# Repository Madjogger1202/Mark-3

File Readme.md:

# Mark 3 — Robot Dog Control Board

> High-current RP2350B-based controller board for quadruped robots.  
> Integrated **battery protection**, **PD charging**, **per-leg power domains**, and **radio/IMU** subsystem.  
> Designed for compact 4-legged robots with modular legs and high servo load.

---

## What’s on the board
- **Main MCU:** RP2350B (USB-programmable)
- **Power system:**
  - **6 × 18650** cells in **parallel** (on-board holders)
  - **Protection IC:** DW01 for undervoltage / overcurrent safety  
  - **USB Type-C PD** charging via **HUSB237-AA001-DN06R** (default 15 V profile, configurable)
  - **Battery charger:** BQ24610, up to **10 A charge current**
  - **Four TPS61088** boost converters — each provides **6 V / 10 A** per leg
  - Individual **enable lines** for each leg’s converter
  - **Current-sense** circuit per leg power rail
- **IMU:** LSM6DS3 (SPI interface)
- **Radio:** nRF24L01P (integrated 2.4 GHz transceiver)
- **LED indication:**
  - 8 × battery-level LEDs
  - 2 × status LEDs (power / charging / fault)
- **Two separate USB-C ports:**
  - **Programming** (direct to RP2350B)
  - **Charging** (PD trigger + BQ24610)
- **BOOT** button for UF2 flashing  
- All power and signal routing optimized for servo current spikes

---

## Power System Overview
| Function | Component | Voltage | Current | Notes |
|:--|:--|:--|:--|:--|
| PD Trigger | HUSB237-AA001-DN06R | 15 V (default) | up to 3 A | Configurable by resistors |
| Charger | BQ24610 | 15 V → Battery | up to 10 A | 1S6P Li-ion |
| Protection | DW01 | 1S | — | Undervoltage / overcurrent cutoff |
| Boost × 4 | TPS61088 | 6 V | 10 A each | One per leg |
| MCU & Logic | RP2350B + LDO | 3.3 V | — | Isolated domain |

> ⚠️ **Do not** connect external 5 V to the MCU port while PD charging.  
> Power and data paths are separate to prevent back-feed.

---

## Sensors & Interfaces
- **LSM6DS3 (SPI)** — motion sensing (accelerometer + gyroscope)  
- **nRF24L01P (SPI)** — wireless communication  
- Expansion headers for extra sensors (I²C / SPI / UART)  
- Servo outputs grouped per leg (3 per leg × 4 legs)

---

## Battery Section
- 6 × **18650 cells in parallel**
- **DW01** provides basic protection (no balancing)
- On-board holders for easy replacement
- **LED bar (8 segments)** for charge level indication

---

## Quick Use
1. Insert 6× 18650 cells into holders.  
2. Connect USB-C **charging** port (PD trigger negotiates 15 V).  
3. Wait for charge LEDs to show full battery.  
4. Connect USB-C **programming** port to PC.  
5. Hold **BOOT** and power the board to enter UF2 mode.  
6. Flash firmware to RP2350B.  
7. Control each leg’s power domain and read current measurements as needed.

---

## Typical Applications
- Quadruped robots (up to 4 legs, 3 servos per leg)
- High-current servo testing rigs
- Portable motion control platforms
- Development base for RP2350 motion control firmware

---

## Notes
- Each leg’s 6 V converter (TPS61088) can be disabled via GPIO.  
- Charging and MCU USB ports are independent.  
- PD trigger default = 15 V (can be changed by resistor network).  
- Full pinout and schematics in `/docs/Mark3_schematic.pdf`.

---

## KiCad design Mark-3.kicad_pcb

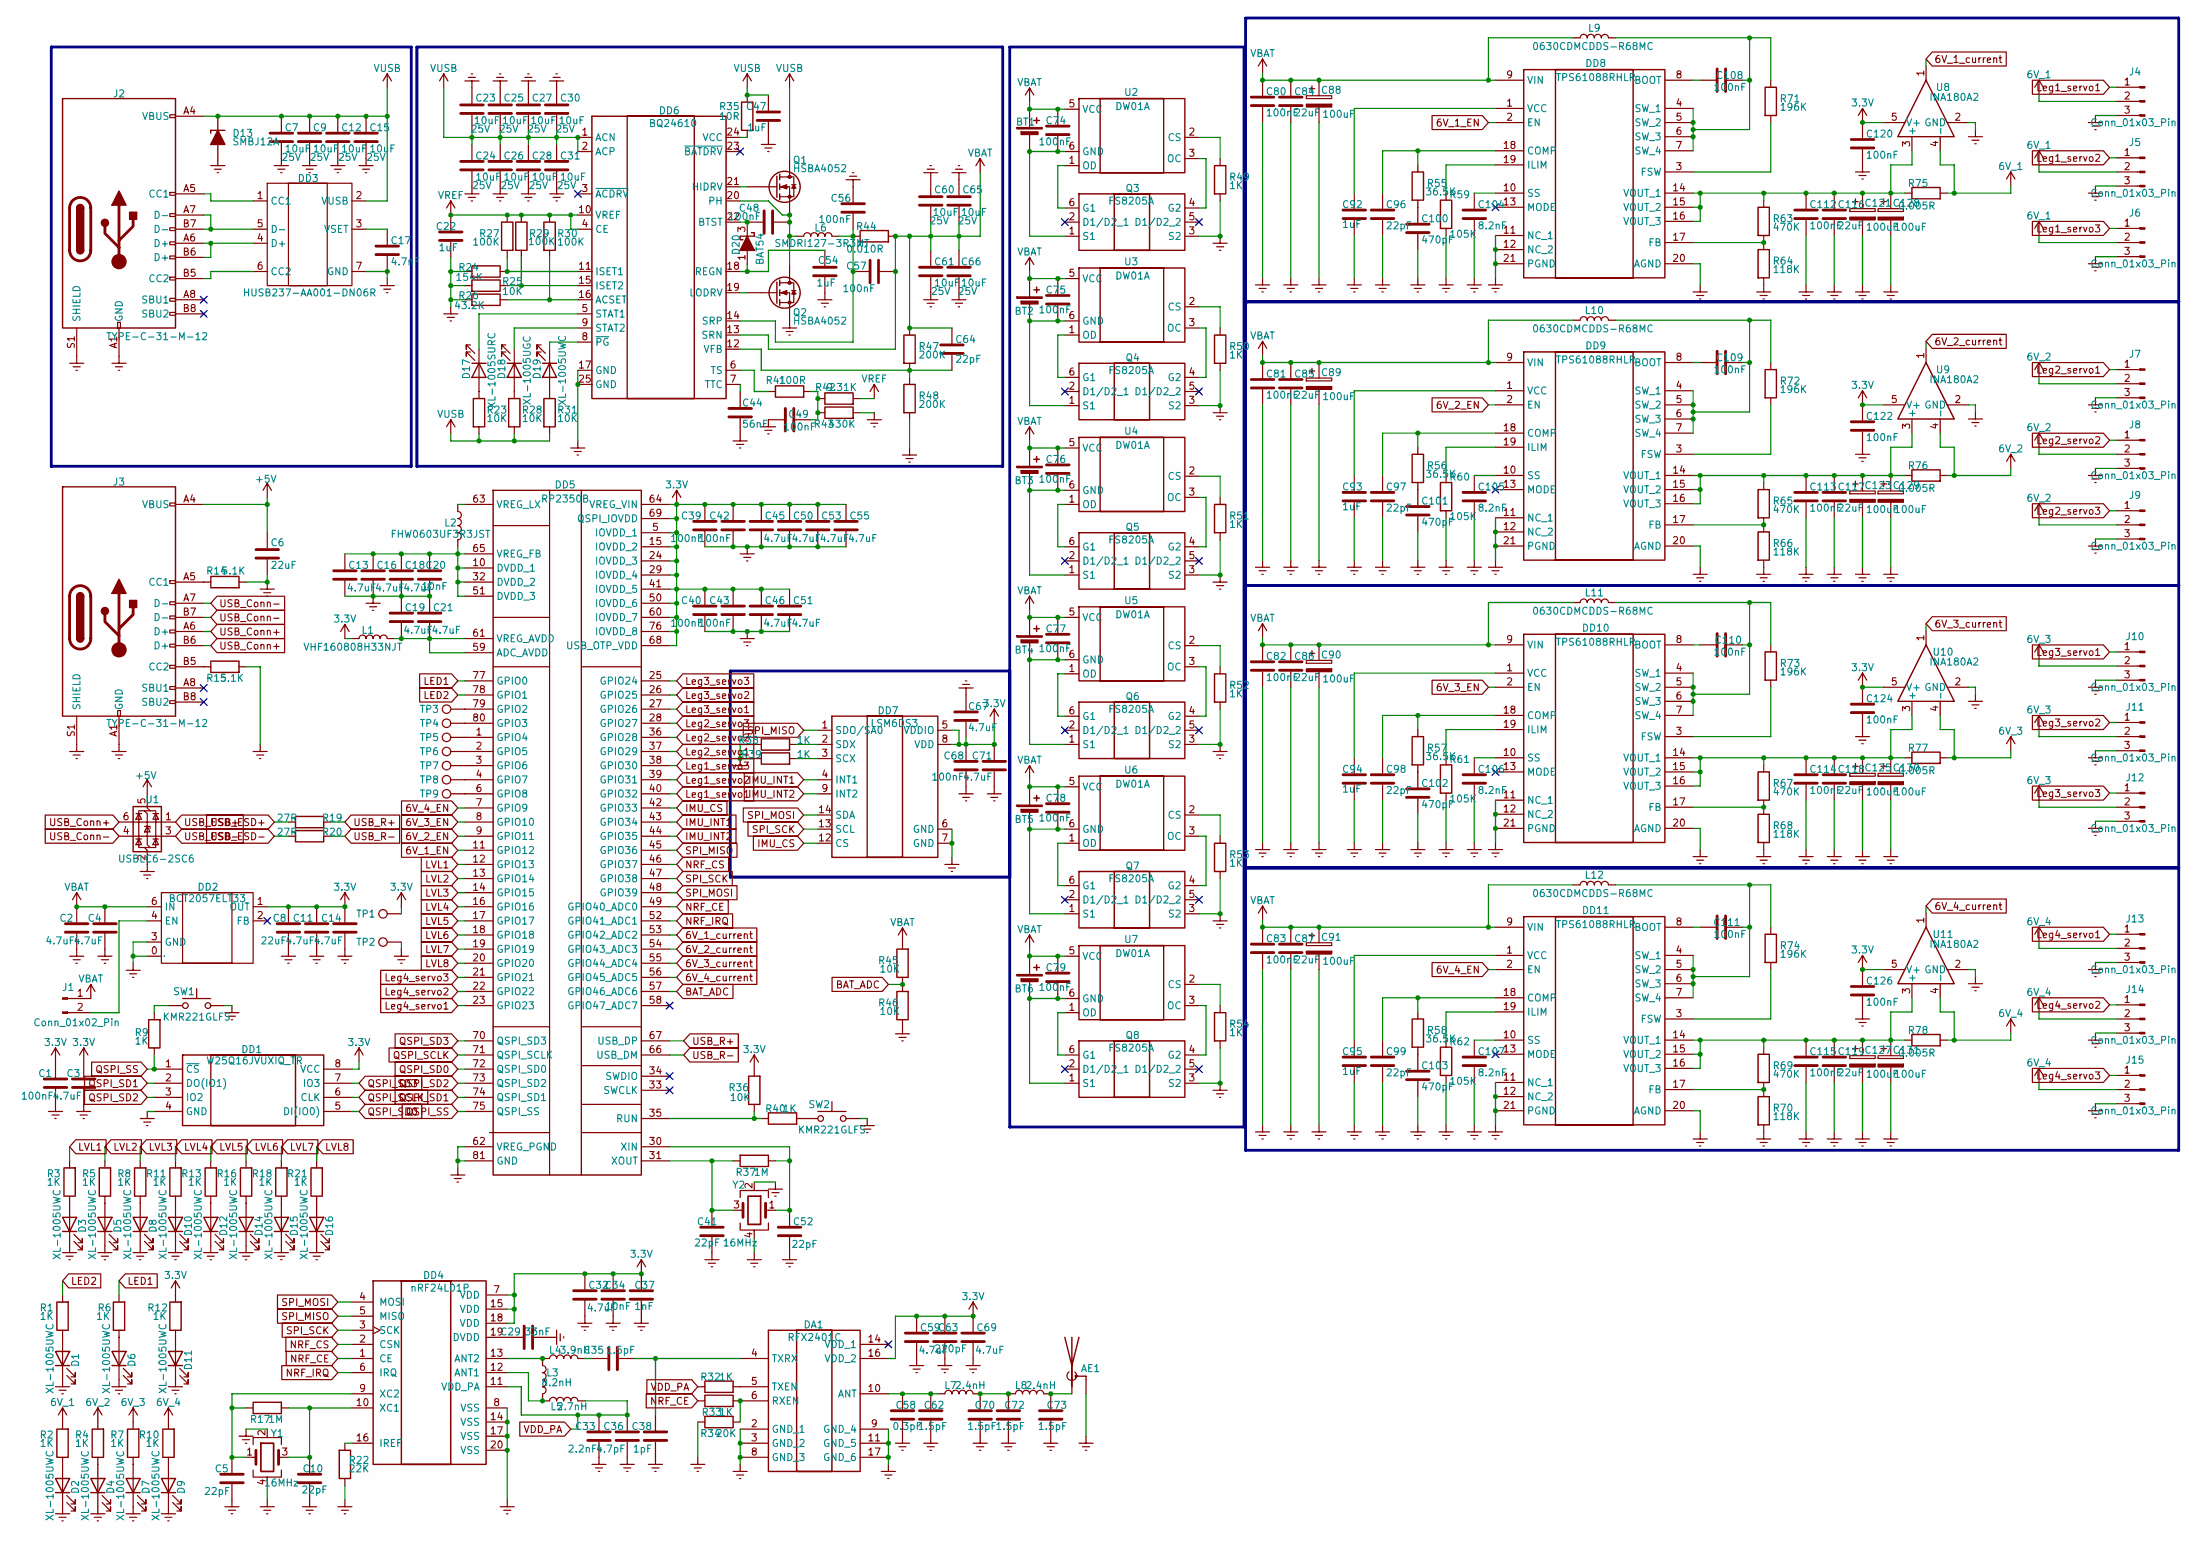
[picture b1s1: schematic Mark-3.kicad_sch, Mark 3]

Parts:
AE1: Antenna_Shield; Texas_SWRA117D_2.4GHz_Right
BT1, BT2, BT3, BT4, BT5, BT6: Battery_Cell; BatteryHolder_Keystone_1042_1x18650
C1, C39, C40, C42, C43, C68: 100nF; C_0201_0603Metric
C2, C3, C4, C11, C13, C14, C16, C18, C19, C21, C32, C45, C46, C50, C51, C53, C55, C59, C67, C69, C71: 4.7uF; C_0201_0603Metric
C5, C10, C41, C52: 22pF; C_0201_0603Metric
C6, C8: 22uF; C_0402_1005Metric
C7, C9, C12, C15, C23, C24, C25, C26, C27, C28, C30, C31, C60, C61, C65, C66: 10uF; C_0805_2012Metric; Voltage 25V; JLCPCB part C5674
C17: 4.7nF; C_0402_1005Metric; JLCPCB part C5674
C20, C34: 10nF; C_0201_0603Metric
C22, C47, C54, C92, C93, C94, C95: 1uF; C_0402_1005Metric; JLCPCB part C5674
C29: 33nF; C_0201_0603Metric
C33: 2.2nF; C_0201_0603Metric
C35, C62, C70, C72, C73: 1.5pF; C_0201_0603Metric
C36: 4.7pF; C_0201_0603Metric
C37: 1nF; C_0201_0603Metric
C38: 1pF; C_0201_0603Metric
C44: 56nF; C_0402_1005Metric; JLCPCB part C5674
C48, C49, C56, C57, C74, C75, C76, C77, C78, C79, C80, C81, C82, C83, C108, C109, C110, C111, C112, C113, C114, C115, C120, C122, C124, C126: 100nF; C_0402_1005Metric; JLCPCB part C5674
C58: 0.3pF; C_0201_0603Metric
C63: 220pF; C_0201_0603Metric
C64, C96, C97, C98, C99: 22pF; C_0402_1005Metric; JLCPCB part C5674
C84, C85, C86, C87, C116, C117, C118, C119: 22uF; C_0805_2012Metric; JLCPCB part C5674
C88, C89, C90, C91, C121, C123, C125, C127, C128, C129, C130, C131: 100uF; CP_EIA-3528-21_Kemet-B; JLCPCB part C140381
C100, C101, C102, C103: 470pF; C_0402_1005Metric; JLCPCB part C5674
C104, C105, C106, C107: 8.2nF; C_0402_1005Metric; JLCPCB part C5674
D1, D2, D3, D4, D5, D6, D7, D8, D9, D10, D11, D12, D14, D15, D16, D19: XL-1005UWC; LED_0402_1005Metric
D13: SMBJ12A; D_SMB
D17: XL-1005SURC; LED_0402_1005Metric
D18: XL-1005UGC; LED_0402_1005Metric
D20: BAT54; SOT-23
DA1: RFX2401C; Manufacturer_Part_Number RFX2401C; Mouser Part Number 477-RFX2401C
DD1: W25Q16JVUXIQ_TR; W25Q16JVUXIQ; Manufacturer_Part_Number W25Q16JVUXIQ TR; Mouser Part Number 454-W25Q16JVUXIQTR
DD2: BCT2057ELT33; BCT2057ELTAJ; Manufacturer Part BCT2057ELTAJ-TR; LCSC Part Name 1A, 低 dropout 线性稳压器
DD3: HUSB237-AA001-DN06R; Manufacturer Part HUSB237-AA001-DN06R; LCSC Part Name HUSB237-AA001-DN06R
DD4: nRF24L01P; QFN-20-1EP_4x4mm_P0.5mm_EP2.5x2.5mm
DD5: RP2350B; QFN40P1000X1000X90-81N-D; Manufacturer_Part_Number RP2350B
DD6: BQ24610; VQFN-24-1EP_4x4mm_P0.5mm_EP2.45x2.45mm
DD7: LSM6DS3; LGA-14_3x2.5mm_P0.5mm_LayoutBorder3x4y
DD8, DD9, DD10, DD11: TPS61088RHLR; Manufacturer_Part_Number TPS61088RHLR; Mouser Part Number 595-TPS61088RHLR
J1: Conn_01x02_Pin; PinHeader_1x02_P2.54mm_Vertical
J2: TYPE-C-31-M-12; USB_C_Receptacle_G-Switch_GT-USB-7010ASV
J3: TYPE-C-31-M-12; USB_C_Receptacle_GCT_USB4105-xx-A_16P_TopMnt_Horizontal
J4, J5, J6, J7, J8, J9, J10, J11, J12, J13, J14, J15: Conn_01x03_Pin; PinHeader_1x03_P2.54mm_Vertical
L1: VHF160808H33NJT; L_0603_1608Metric
L2: FHW0603UF3R3JST; L_0603_1608Metric
L3: 8.2nH; L_0201_0603Metric
L4: 3.9nH; L_0201_0603Metric
L5: 2.7nH; L_0201_0603Metric
L6: SMDRI127-3R3MT; L_SXN_SMDRI127
L7, L8: 2.4nH; L_0201_0603Metric
L9, L10, L11, L12: 0630CDMCDDS-R68MC; L_Sunlord_MWSA0603S
Q1, Q2: HSBA4052; PQFN-8-EP_6x5mm_P1.27mm_Generic
Q3, Q4, Q5, Q6, Q7, Q8: FS8205A; Manufacturer_Part_Number FS8205A
R1, R2, R3, R4, R5, R6, R7, R8, R10, R11, R12, R13, R16, R18, R21, R49, R50, R51, R52, R53, R54: 1K; R_0402_1005Metric
R9, R32, R33, R38, R39, R40: 1K; R_0201_0603Metric
R14, R15: 5.1K; R_0402_1005Metric
R17, R37: 1M; R_0201_0603Metric
R19, R20: 27R; R_0201_0603Metric
R22: 22K; R_0201_0603Metric
R23, R25, R28, R31: 10K; R_0402_1005Metric
R24: 154K; R_0402_1005Metric
R26: 43.2K; R_0402_1005Metric
R27, R29, R30: 100K; R_0402_1005Metric
R34: 20K; R_0201_0603Metric
R35: 10R; R_0402_1005Metric
R36, R45, R46: 10K; R_0201_0603Metric
R41: 100R; R_0402_1005Metric
R42: 9.31K; R_0402_1005Metric
R43: 430K; R_0402_1005Metric
R44: 0.010R; R_2512_6332Metric_Pad1.40x3.35mm
R47, R48: 200K; R_0402_1005Metric
R55, R56, R57, R58: 36.5K; R_0402_1005Metric
R59, R60, R61, R62: 105K; R_0402_1005Metric
R63, R65, R67, R69: 470K; R_0402_1005Metric
R64, R66, R68, R70: 118K; R_0402_1005Metric
R71, R72, R73, R74: 196K; R_0402_1005Metric
R75, R76, R77, R78: 0.005R; R_1206_3216Metric
SW1, SW2: KMR221GLFS; SW_SPST_PTS810
TP1, TP2, TP3, TP4, TP5, TP6, TP7, TP8, TP9: TestPoint; TestPoint_Pad_D1.0mm
U1: USBLC6-2SC6; SOT-23-6
U2, U3, U4, U5, U6, U7: DW01A; SOT-23-6
U8, U9, U10, U11: INA180A2; SOT-23-5
Y1, Y2: 16MHz; Crystal_SMD_3225-4Pin_3.2x2.5mm

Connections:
3.3V: C1.1, C3.1, C8.1, C11.1, C14.1, C32.1, C34.1, C37.1, C39.1, C40.1, C42.1, C43.1, C45.1, C46.1, C50.1, C51.1, C53.1, C55.1, C59.1, C63.1, C67.1, C68.1, C69.1, C71.1, C120.1, C122.1, C124.1, C126.1, DA1.16 (VDD_2), DD1.8 (VCC), DD2.1 (OUT), DD4.7 (VDD), DD4.15 (VDD), DD4.18 (VDD), DD5.5 (IOVDD_1), DD5.15 (IOVDD_2), DD5.24 (IOVDD_3), DD5.29 (IOVDD_4), DD5.41 (IOVDD_5), DD5.50 (IOVDD_6), DD5.60 (IOVDD_7), DD5.64 (VREG_VIN), DD5.68 (USB_OTP_VDD), DD5.69 (QSPI_IOVDD), DD5.76 (IOVDD_8), DD7.5 (VDDIO), DD7.8 (VDD), L1.1, R12.2, R36.2, TP1.1, U8.5 (V+), U9.5 (V+), U10.5 (V+), U11.5 (V+)
6V_1: J4.2, J5.2, J6.2, R2.2, R75.2, U8.4 (-)
6V_1_EN: DD5.11 (GPIO12), DD8.2 (EN)
6V_1_current: DD5.53 (GPIO42_ADC2), U8.1
6V_2: J7.2, J8.2, J9.2, R4.2, R76.2, U9.4 (-)
6V_2_EN: DD5.9 (GPIO11), DD9.2 (EN)
6V_2_current: DD5.54 (GPIO43_ADC3), U9.1
6V_3: J10.2, J11.2, J12.2, R7.2, R77.2, U10.4 (-)
6V_3_EN: DD5.8 (GPIO10), DD10.2 (EN)
6V_3_current: DD5.55 (GPIO44_ADC4), U10.1
6V_4: J13.2, J14.2, J15.2, R10.2, R78.2, U11.4 (-)
6V_4_EN: DD5.7 (GPIO9), DD11.2 (EN)
6V_4_current: DD5.56 (GPIO45_ADC5), U11.1
+5V: C6.1, J3.A4 (VBUS), J3.A9 (VBUS), J3.B4 (VBUS), J3.B9 (VBUS), U1.5 (VBUS)
BAT_ADC: DD5.57 (GPIO46_ADC6), R45.1, R46.2
Earth: AE1.2 (Shield), C1.2, C2.2, C3.2, C4.2, C5.2, C6.2, C7.2, C8.2, C9.2, C10.2, C11.2, C12.2, C13.2, C14.2, C15.2, C16.2, C17.2, C18.2, C19.1, C20.2, C21.1, C22.2, C23.2, C24.2, C25.2, C26.2, C27.2, C28.2, C29.2, C30.2, C31.2, C32.2, C33.2, C34.2, C36.2, C37.2, C38.2, C39.2, C40.2, C41.2, C42.2, C43.2, C44.2, C45.2, C46.2, C47.1, C49.1, C50.2, C51.2, C52.2, C53.2, C54.1, C55.2, C56.2, C58.2, C59.2, C60.2, C61.2, C62.2, C63.2, C65.2, C66.2, C67.2, C68.2, C69.2, C70.2, C71.2, C72.2, C73.2, C80.2, C81.2, C82.2, C83.2, C84.2, C85.2, C86.2, C87.2, C88.2, C89.2, C90.2, C91.2, C92.2, C93.2, C94.2, C95.2, C96.2, C97.2, C98.2, C99.2, C100.2, C101.2, C102.2, C103.2, C104.2, C105.2, C106.2, C107.2, C112.2, C113.2, C114.2, C115.2, C116.2, C117.2, C118.2, C119.2, C120.2, C121.2, C122.2, C123.2, C124.2, C125.2, C126.2, C127.2, C128.2, C129.2, C130.2, C131.2, D1.1 (K), D2.1 (K), D3.1 (K), D4.1 (K), D5.1 (K), D6.1 (K), D7.1 (K), D8.1 (K), D9.1 (K), D10.1 (K), D11.1 (K), D12.1 (K), D13.2 (A), D14.1 (K), D15.1 (K), D16.1 (K), DA1.2 (GND_1), DA1.3 (GND_2), DA1.8 (GND_3), DA1.9 (GND_4), DA1.11 (GND_5), DA1.17 (GND_6), DD1.4 (GND), DD2.0 (EP), DD2.3 (GND), DD3.7 (GND), DD4.8 (VSS), DD4.14 (VSS), DD4.17 (VSS), DD4.20 (VSS), DD4.21 (PAD), DD5.62 (VREG_PGND), DD5.81 (GND), DD6.17 (GND), DD6.25 (GND), DD7.6 (GND), DD7.7 (GND), DD8.11 (NC_1), DD8.12 (NC_2), DD8.20 (AGND), DD8.21 (PGND), DD9.11 (NC_1), DD9.12 (NC_2), DD9.20 (AGND), DD9.21 (PGND), DD10.11 (NC_1), DD10.12 (NC_2), DD10.20 (AGND), DD10.21 (PGND), DD11.11 (NC_1), DD11.12 (NC_2), DD11.20 (AGND), DD11.21 (PGND), J2.A1 (GND), J2.A12 (GND), J2.B1 (GND), J2.B12 (GND), J2.S1 (SHIELD), J3.A1 (GND), J3.A12 (GND), J3.B1 (GND), J3.B12 (GND), J3.S1 (SHIELD), J4.3, J5.3, J6.3, J7.3, J8.3, J9.3, J10.3, J11.3, J12.3, J13.3, J14.3, J15.3, Q2.1 (S), Q2.2 (S), Q2.3 (S), Q3.3 (S2), Q4.3 (S2), Q5.3 (S2), Q6.3 (S2), Q7.3 (S2), Q8.3 (S2), R14.2, R15.2, R22.1, R24.2, R25.2, R26.2, R34.2, R38.1, R39.1, R43.2, R46.1, R48.2, R49.2, R50.2, R51.2, R52.2, R53.2, R54.2, R59.2, R60.2, R61.2, R62.2, R64.2, R66.2, R68.2, R70.2, SW1.1, SW2.1, TP2.1, U1.2 (GND), U8.2 (GND), U9.2 (GND), U10.2 (GND), U11.2 (GND), Y1.2, Y1.4, Y2.2, Y2.4
IMU_CS: DD5.42 (GPIO33), DD7.12 (CS)
IMU_INT1: DD5.43 (GPIO34), DD7.4 (INT1)
IMU_INT2: DD5.44 (GPIO35), DD7.9 (INT2)
LED1: DD5.77 (GPIO0), R6.2
LED2: DD5.78 (GPIO1), R1.2
LVL1: DD5.12 (GPIO13), R3.2
LVL2: DD5.13 (GPIO14), R5.2
LVL3: DD5.14 (GPIO15), R8.2
LVL4: DD5.16 (GPIO16), R11.2
LVL5: DD5.17 (GPIO17), R13.2
LVL6: DD5.18 (GPIO18), R16.2
LVL7: DD5.19 (GPIO19), R18.2
LVL8: DD5.20 (GPIO20), R21.2
Leg1_servo1: DD5.40 (GPIO32), J4.1
Leg1_servo2: DD5.39 (GPIO31), J5.1
Leg1_servo3: DD5.38 (GPIO30), J6.1
Leg2_servo1: DD5.37 (GPIO29), J7.1
Leg2_servo2: DD5.36 (GPIO28), J8.1
Leg2_servo3: DD5.28 (GPIO27), J9.1
Leg3_servo1: DD5.27 (GPIO26), J10.1
Leg3_servo2: DD5.26 (GPIO25), J11.1
Leg3_servo3: DD5.25 (GPIO24), J12.1
Leg4_servo1: DD5.23 (GPIO23), J13.1
Leg4_servo2: DD5.22 (GPIO22), J14.1
Leg4_servo3: DD5.21 (GPIO21), J15.1
NRF_CE: DD4.1 (CE), DD5.49 (GPIO40_ADC0), R33.1
NRF_CS: DD4.2 (CSN), DD5.46 (GPIO37)
NRF_IRQ: DD4.6 (IRQ), DD5.52 (GPIO41_ADC1)
unnamed: AE1.1 (A), C73.1, L8.2
unnamed: BT1.2 (-), C74.2, Q3.1 (S1), U2.6 (GND)
unnamed: BT2.2 (-), C75.2, Q4.1 (S1), U3.6 (GND)
unnamed: BT3.2 (-), C76.2, Q5.1 (S1), U4.6 (GND)
unnamed: BT4.2 (-), C77.2, Q6.1 (S1), U5.6 (GND)
unnamed: BT5.2 (-), C78.2, Q7.1 (S1), U6.6 (GND)
unnamed: BT6.2 (-), C79.2, Q8.1 (S1), U7.6 (GND)
unnamed: C35.1, L4.2
unnamed: C49.2, R41.2, R42.1, R43.1
unnamed: C70.1, C72.1, L7.2, L8.1
unnamed: C100.1, R55.2
unnamed: C101.1, R56.2
unnamed: C102.1, R57.2
unnamed: C103.1, R58.2
unnamed: D1.2 (A), R1.1
unnamed: D2.2 (A), R2.1
unnamed: D3.2 (A), R3.1
unnamed: D4.2 (A), R4.1
unnamed: D5.2 (A), R5.1
unnamed: D6.2 (A), R6.1
unnamed: D7.2 (A), R7.1
unnamed: D8.2 (A), R8.1
unnamed: D9.2 (A), R10.1
unnamed: D10.2 (A), R11.1
unnamed: D11.2 (A), R12.1
unnamed: D12.2 (A), R13.1
unnamed: D14.2 (A), R16.1
unnamed: D15.2 (A), R18.1
unnamed: D16.2 (A), R21.1
unnamed: D17.2 (A), R23.1
unnamed: D17.1 (K), DD6.5 (STAT1)
unnamed: D18.2 (A), R28.1
unnamed: D18.1 (K), DD6.9 (STAT2)
unnamed: D19.2 (A), R31.1
unnamed: D19.1 (K), DD6.8 (~PG)
unnamed: C54.2, D20.1 (A), DD6.18 (REGN)
unnamed: C48.1, D20.3 (K), DD6.22 (BTST)
unnamed: C58.1, C62.1, DA1.10 (ANT), L7.1
unnamed: DA1.6 (RXEN), R33.2, R34.1
unnamed: DA1.5 (TXEN), R32.2
unnamed: C35.2, C38.1, DA1.4 (TXRX)
unnamed: DD2.4 (EN), J1.2
unnamed: DD3.1 (CC1), J2.A5 (CC1)
unnamed: DD3.6 (CC2), J2.B5 (CC2)
unnamed: DD3.4 (D+), J2.A6 (D+), J2.B6 (D+)
unnamed: DD3.5 (D-), J2.A7 (D-), J2.B7 (D-)
unnamed: C17.1, DD3.3 (VSET)
unnamed: DD4.12 (ANT1), L3.2, L5.1
unnamed: DD4.13 (ANT2), L3.1, L4.1
unnamed: C29.1, DD4.19 (DVDD)
unnamed: DD4.16 (IREF), R22.2
unnamed: C10.1, DD4.10 (XC1), R17.2, Y1.3
unnamed: C5.1, DD4.9 (XC2), R17.1, Y1.1
unnamed: C19.2, C21.2, DD5.59 (ADC_AVDD), DD5.61 (VREG_AVDD), L1.2
unnamed: C13.1, C16.1, C18.1, C20.1, DD5.10 (DVDD_1), DD5.32 (DVDD_2), DD5.51 (DVDD_3), DD5.65 (VREG_FB), L2.2
unnamed: DD5.79 (GPIO2), TP3.1
unnamed: DD5.80 (GPIO3), TP4.1
unnamed: DD5.1 (GPIO4), TP5.1
unnamed: DD5.2 (GPIO5), TP6.1
unnamed: DD5.3 (GPIO6), TP7.1
unnamed: DD5.4 (GPIO7), TP8.1
unnamed: DD5.6 (GPIO8), TP9.1
unnamed: DD5.35 (RUN), R36.1, R40.1
unnamed: DD5.63 (VREG_LX), L2.1
unnamed: C52.1, DD5.30 (XIN), R37.1, Y2.1
unnamed: C41.1, DD5.31 (XOUT), R37.2, Y2.3
unnamed: DD6.16 (ACSET), R26.1, R30.2
unnamed: DD6.21 (HIDRV), Q1.4 (G)
unnamed: DD6.11 (ISET1), R24.1, R27.2
unnamed: DD6.15 (ISET2), R25.1, R29.2
unnamed: DD6.19 (LODRV), Q2.4 (G)
unnamed: C56.1, C57.1, DD6.14 (SRP), L6.2, R44.1
unnamed: DD6.6 (TS), R41.1
unnamed: C44.1, DD6.7 (TTC)
unnamed: DD6.24 (VCC), R35.2
unnamed: C64.2, DD6.12 (VFB), R47.2, R48.1
unnamed: DD7.3 (SCX), R39.2
unnamed: DD7.2 (SDX), R38.2
unnamed: C108.1, DD8.8 (BOOT)
unnamed: C96.1, DD8.18 (COMP), R55.1
unnamed: DD8.17 (FB), R63.2, R64.1
unnamed: DD8.3 (FSW), R71.2
unnamed: DD8.19 (ILIM), R59.1
unnamed: C104.1, DD8.10 (SS)
unnamed: C108.2, DD8.4 (SW_1), DD8.5 (SW_2), DD8.6 (SW_3), DD8.7 (SW_4), L9.2, R71.1
unnamed: C92.1, DD8.1 (VCC)
unnamed: C112.1, C116.1, C121.1, C128.1, DD8.14 (VOUT_1), DD8.15 (VOUT_2), DD8.16 (VOUT_3), R63.1, R75.1, U8.3 (+)
unnamed: C109.1, DD9.8 (BOOT)
unnamed: C97.1, DD9.18 (COMP), R56.1
unnamed: DD9.17 (FB), R65.2, R66.1
unnamed: DD9.3 (FSW), R72.2
unnamed: DD9.19 (ILIM), R60.1
unnamed: C105.1, DD9.10 (SS)
unnamed: C109.2, DD9.4 (SW_1), DD9.5 (SW_2), DD9.6 (SW_3), DD9.7 (SW_4), L10.2, R72.1
unnamed: C93.1, DD9.1 (VCC)
unnamed: C113.1, C117.1, C123.1, C129.1, DD9.14 (VOUT_1), DD9.15 (VOUT_2), DD9.16 (VOUT_3), R65.1, R76.1, U9.3 (+)
unnamed: C110.1, DD10.8 (BOOT)
unnamed: C98.1, DD10.18 (COMP), R57.1
unnamed: DD10.17 (FB), R67.2, R68.1
unnamed: DD10.3 (FSW), R73.2
unnamed: DD10.19 (ILIM), R61.1
unnamed: C106.1, DD10.10 (SS)
unnamed: C110.2, DD10.4 (SW_1), DD10.5 (SW_2), DD10.6 (SW_3), DD10.7 (SW_4), L11.2, R73.1
unnamed: C94.1, DD10.1 (VCC)
unnamed: C114.1, C118.1, C125.1, C130.1, DD10.14 (VOUT_1), DD10.15 (VOUT_2), DD10.16 (VOUT_3), R67.1, R77.1, U10.3 (+)
unnamed: C111.1, DD11.8 (BOOT)
unnamed: C99.1, DD11.18 (COMP), R58.1
unnamed: DD11.17 (FB), R69.2, R70.1
unnamed: DD11.3 (FSW), R74.2
unnamed: DD11.19 (ILIM), R62.1
unnamed: C107.1, DD11.10 (SS)
unnamed: C111.2, DD11.4 (SW_1), DD11.5 (SW_2), DD11.6 (SW_3), DD11.7 (SW_4), L12.2, R74.1
unnamed: C95.1, DD11.1 (VCC)
unnamed: C115.1, C119.1, C127.1, C131.1, DD11.14 (VOUT_1), DD11.15 (VOUT_2), DD11.16 (VOUT_3), R69.1, R78.1, U11.3 (+)
unnamed: J3.A5 (CC1), R14.1
unnamed: J3.B5 (CC2), R15.1
unnamed: Q3.6 (G1), U2.1 (OD)
unnamed: Q3.4 (G2), U2.3 (OC)
unnamed: Q4.6 (G1), U3.1 (OD)
unnamed: Q4.4 (G2), U3.3 (OC)
unnamed: Q5.6 (G1), U4.1 (OD)
unnamed: Q5.4 (G2), U4.3 (OC)
unnamed: Q6.6 (G1), U5.1 (OD)
unnamed: Q6.4 (G2), U5.3 (OC)
unnamed: Q7.6 (G1), U6.1 (OD)
unnamed: Q7.4 (G2), U6.3 (OC)
unnamed: Q8.6 (G1), U7.1 (OD)
unnamed: Q8.4 (G2), U7.3 (OC)
unnamed: R9.2, SW1.2
unnamed: R40.2, SW2.2
unnamed: R49.1, U2.2 (CS)
unnamed: R50.1, U3.2 (CS)
unnamed: R51.1, U4.2 (CS)
unnamed: R52.1, U5.2 (CS)
unnamed: R53.1, U6.2 (CS)
unnamed: R54.1, U7.2 (CS)
QSPI_SCLK: DD1.6 (CLK), DD5.71 (QSPI_SCLK)
QSPI_SD0: DD1.5 (DI(IO0)), DD5.72 (QSPI_SD0)
QSPI_SD1: DD1.2 (DO(IO1)), DD5.74 (QSPI_SD1)
QSPI_SD2: DD1.3 (IO2), DD5.73 (QSPI_SD2)
QSPI_SD3: DD1.7 (IO3), DD5.70 (QSPI_SD3)
QSPI_SS: DD1.1 (~CS), DD5.75 (QSPI_SS), R9.1
SPI_MISO: DD4.5 (MISO), DD5.45 (GPIO36), DD7.1 (SDO/SA0)
SPI_MOSI: DD4.4 (MOSI), DD5.48 (GPIO39), DD7.14 (SDA)
SPI_SCK: DD4.3 (SCK), DD5.47 (GPIO38), DD7.13 (SCL)
USB_Conn+: J3.A6 (D+), J3.B6 (D+), U1.6 (I/O1)
USB_Conn-: J3.A7 (D-), J3.B7 (D-), U1.4 (I/O2)
USB_ESD+: R19.2, U1.1 (I/O1)
USB_ESD-: R20.2, U1.3 (I/O2)
USB_R+: DD5.67 (USB_DP), R19.1
USB_R-: DD5.66 (USB_DM), R20.1
VBAT: BT1.1 (+), BT2.1 (+), BT3.1 (+), BT4.1 (+), BT5.1 (+), BT6.1 (+), C2.1, C4.1, C57.2, C60.1, C61.1, C64.1, C65.1, C66.1, C74.1, C75.1, C76.1, C77.1, C78.1, C79.1, C80.1, C81.1, C82.1, C83.1, C84.1, C85.1, C86.1, C87.1, C88.1, C89.1, C90.1, C91.1, DD2.6 (IN), DD6.13 (SRN), DD8.9 (VIN), DD9.9 (VIN), DD10.9 (VIN), DD11.9 (VIN), J1.1, L9.1, L10.1, L11.1, L12.1, R44.2, R45.2, R47.1, U2.5 (VCC), U3.5 (VCC), U4.5 (VCC), U5.5 (VCC), U6.5 (VCC), U7.5 (VCC)
VDD_PA: C33.1, C36.1, DD4.11 (VDD_PA), L5.2, R32.1
VREF: C22.1, DD6.4 (CE), DD6.10 (VREF), R27.1, R29.1, R30.1, R42.2
VUSB: C7.1, C9.1, C12.1, C15.1, C23.1, C24.1, C25.1, C26.1, C27.1, C28.1, C30.1, C31.1, C47.2, D13.1 (K), DD3.2 (VUSB), DD6.1 (ACN), DD6.2 (ACP), J2.A4 (VBUS), J2.A9 (VBUS), J2.B4 (VBUS), J2.B9 (VBUS), Q1.5 (D), R23.2, R28.2, R31.2, R35.1

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
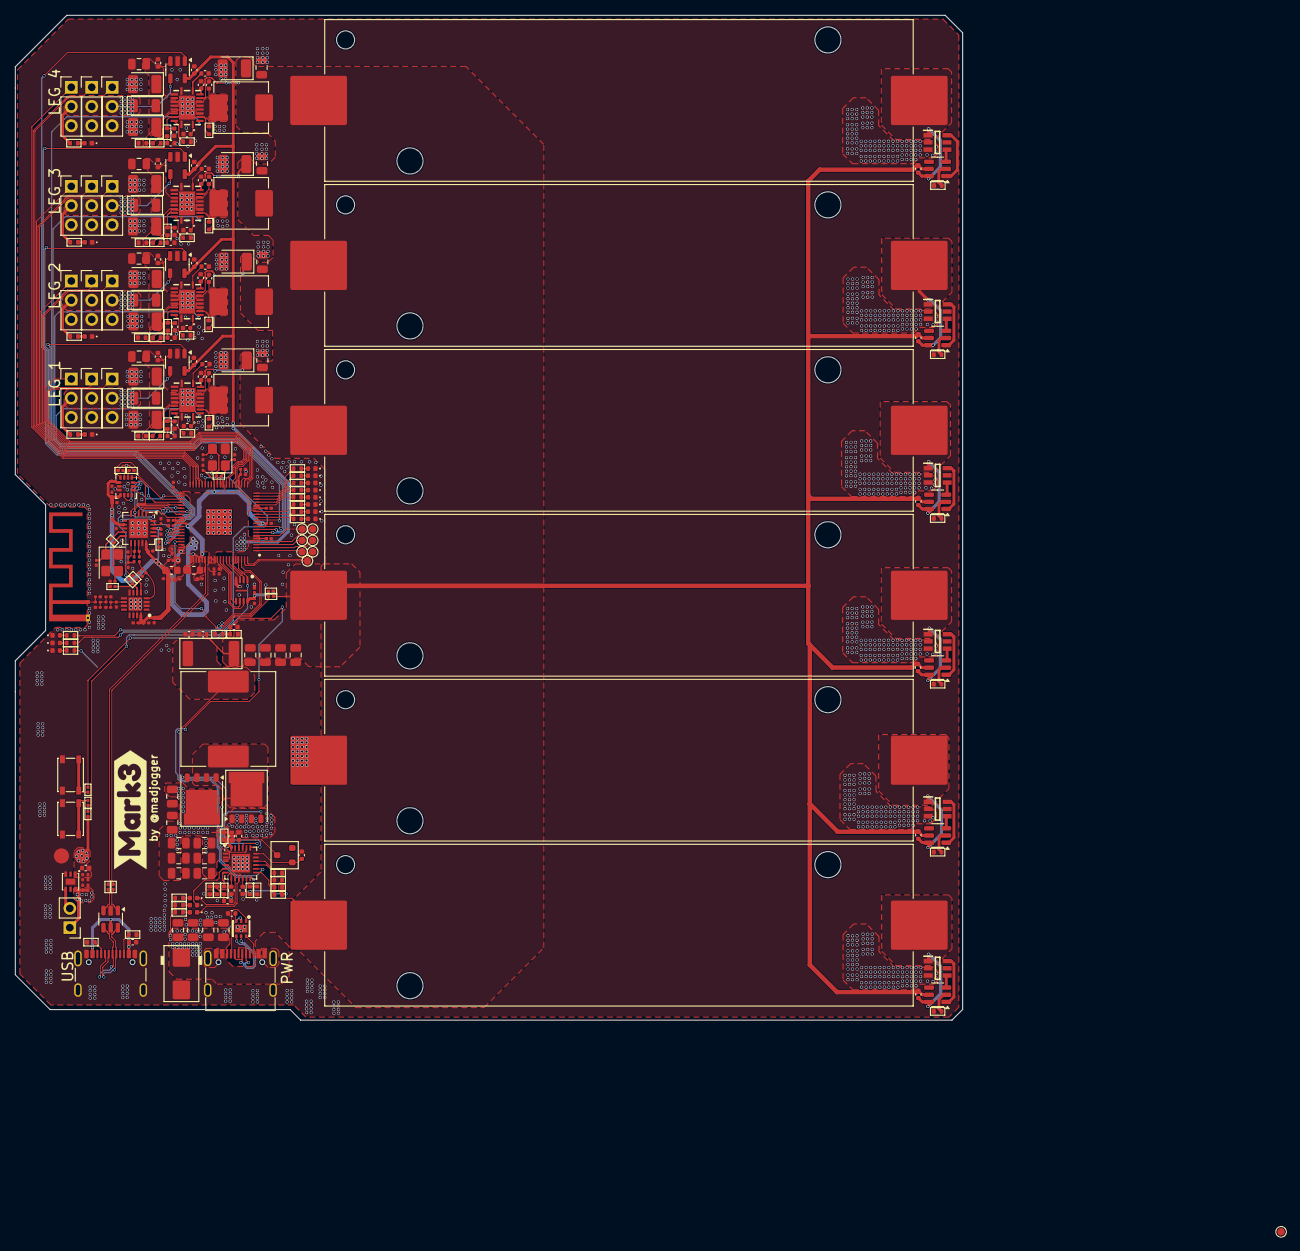
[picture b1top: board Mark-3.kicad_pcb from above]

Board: 2 copper layers, 125.2 x 132.8 mm, 309 parts (0 on the bottom side), 200 nets.

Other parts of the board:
TP8#2: TestPoint; TestPoint_Pad_D1.0mm
kibuzzard-68E68F97: G***; kibuzzard-68E68F97

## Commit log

2025-09-30 initial commit, work in progress
2025-10-02 DC-DC and battery protection circuit done, partly done charger module
2025-10-04 Partly done placement, moving forward to GPIO assigment with placement spec
2025-10-04 UPD schematics
2025-10-05 schematics update
2025-10-08 rev0 ready
2025-10-08 added readme
